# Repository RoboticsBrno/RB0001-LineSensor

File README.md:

# RB0001-LineSensor
Line sensor with 8 sensors for measuring the reflectance of the surface with integrated I2C A/D converter.

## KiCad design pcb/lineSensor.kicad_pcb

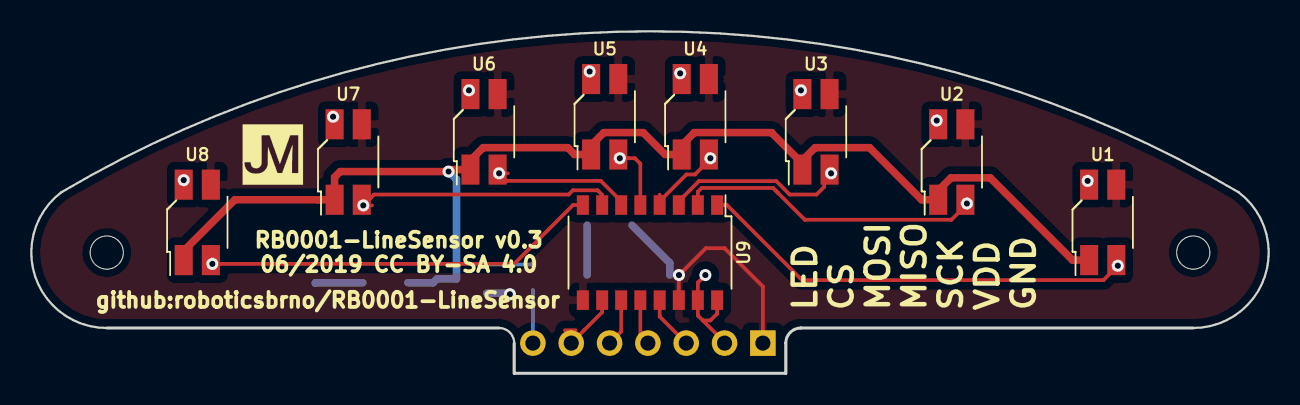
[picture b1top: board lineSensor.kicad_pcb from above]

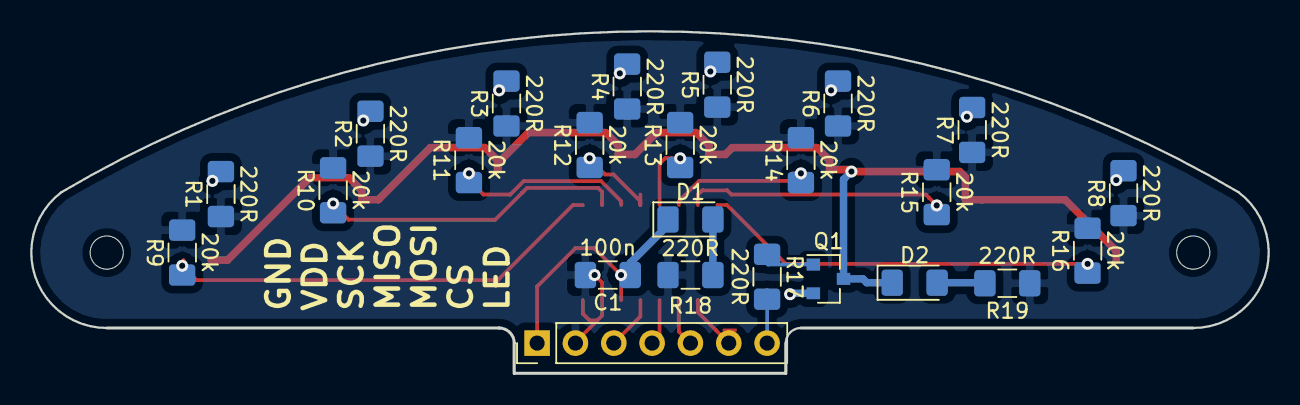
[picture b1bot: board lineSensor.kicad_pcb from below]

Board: 2 copper layers, 81.9 x 22.6 mm, 36 parts (24 on the bottom side), 27 nets.

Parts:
C1: 100n; C_1206_3216Metric_Pad1.42x1.75mm_HandSolder
D1: LED_GREEN; LED_1206_3216Metric_Pad1.42x1.75mm_HandSolder
D2: LED_RED; LED_1206_3216Metric_Pad1.42x1.75mm_HandSolder
J1: Conn_01x07; PinHeader_1x07_P2.54mm_Vertical
MH1, MH2: MountingHole; MountingHole_2.2mm_M2
MH3: MountingHole; JM_4_SILK
Q1: BC817; SOT-23
R1, R2, R3, R4, R5, R6, R7, R8, R17, R18, R19: 220R; R_1206_3216Metric_Pad1.42x1.75mm_HandSolder
R9, R10, R11, R12, R13, R14, R15, R16: 20k; R_1206_3216Metric_Pad1.42x1.75mm_HandSolder
U1, U2, U3, U4, U5, U6, U7, U8: ITR8307; Everlight_ITR8307
U9: MCP3008; SOP-16_4.4x10.4mm_P1.27mm

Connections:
CS: J1.6, U9.10
GND: C1.1, D1.1, J1.1, Q1.2, U1.4, U2.4, U3.4, U4.4, U5.4, U6.4, U7.4, U8.4, U9.9, U9.14
LED_GND: D2.1, Q1.3, U1.1, U2.1, U3.1, U4.1, U5.1, U6.1, U7.1, U8.1
L_EN: J1.7, R17.2
MISO: J1.4, U9.12
MOSI: J1.5, U9.11
unnamed: D1.2, R18.2
unnamed: D2.2, R19.2
unnamed: Q1.1, R17.1
unnamed: R1.2, U1.2
unnamed: R2.2, U2.2
unnamed: R3.2, U3.2
unnamed: R4.2, U4.2
unnamed: R5.2, U5.2
unnamed: R6.2, U6.2
unnamed: R7.2, U7.2
unnamed: R8.2, U8.2
S1: R9.1, U1.3, U9.1
S2: R10.1, U2.3, U9.2
S3: R11.1, U3.3, U9.3
S4: R12.1, U4.3, U9.4
S5: R13.1, U5.3, U9.5
S6: R14.1, U6.3, U9.6
S7: R15.1, U7.3, U9.7
S8: R16.1, U8.3, U9.8
SCK: J1.3, U9.13
VDD: C1.2, J1.2, R1.1, R2.1, R3.1, R4.1, R5.1, R6.1, R7.1, R8.1, R9.2, R10.2, R11.2, R12.2, R13.2, R14.2, R15.2, R16.2, R18.1, R19.1, U9.15, U9.16

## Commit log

2019-06-12 PCB: add initial version of the line sensor board from Jan Mrazek
    - version 0.2 with name SensorLine
2019-06-12 PCB: improve line sensor board
    - change size of SMD parts from 0603 to 1206
    - change name of board from SensorLine to RB0001-LineSensor
    - change version v0.2 to v0.3
    - add license CC BY-SA 4.0
    - add information about repository github:roboticsbrno/RB0001-LineSensor
2019-06-14 PCB: add signalization LEDs, copy pins labels (F.SilkS => B.SilkS)
    - add power and back-light signalization LEDs

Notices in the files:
pcb/lineSensor.kicad_pcb:
06/2019 CC BY-SA 4.0
